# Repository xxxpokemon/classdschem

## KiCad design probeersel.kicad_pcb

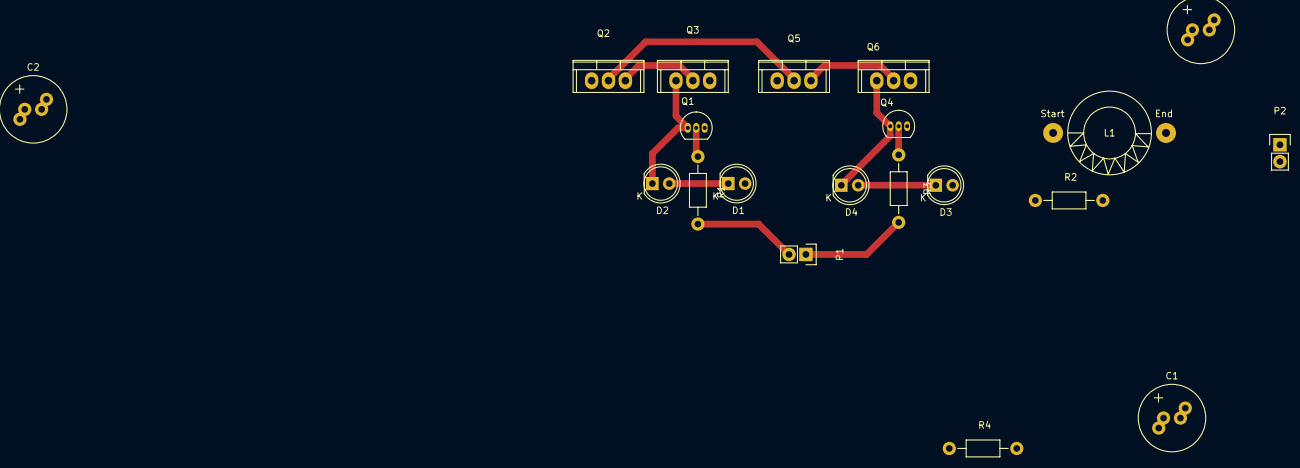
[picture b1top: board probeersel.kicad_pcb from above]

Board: 2 copper layers, 20 parts (0 on the bottom side), 15 nets.

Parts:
C1: 100n; C_Radial_D10_L20_P2.5-5
C2: 330u; C_Radial_D10_L20_P2.5-5
C3: 2.2n; C_Radial_D10_L20_P2.5-5
D1, D2, D3, D4: LED; LED-5MM
L1: INDUCTOR_SMALL; Choke_Toroid_horizontal_Diameter12-5mm_Amidon-T44
P1, P2: CONN_01X02; Pin_Header_Straight_1x02
Q1, Q4: BC547; TO-92_Inline_Narrow_Oval
Q2, Q5: IRF9540N; TO-220
Q3, Q6: IRF540N; TO-220
R1, R3: 10k; Resistor_Horizontal_RM10mm
R2, R4: 1k; Resistor_Horizontal_RM10mm

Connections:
GND: C1.2, C2.2, Q1.3, Q3.3, Q4.3, Q6.3
IN+: P1.2, R1.2
IN-: P1.1, R3.2
unnamed: C1.1, C2.1, Q2.2, Q5.2, R2.1, R4.1
unnamed: C3.1, L1.2, P2.1
unnamed: C3.2, P2.2, Q2.3, Q3.2
unnamed: D1.1, D2.2
unnamed: D1.2, R2.2
unnamed: D2.1, Q1.1, Q3.1
unnamed: D3.1, D4.2
unnamed: D3.2, Q5.1, R4.2
unnamed: D4.1, Q4.1, Q6.1
unnamed: L1.1, Q5.3, Q6.2
unnamed: Q1.2, R1.1
unnamed: Q4.2, R3.1

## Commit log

2015-12-30 new file: probeersel.kicad_pcb new file: probeersel.pro new file: probeersel.sch
